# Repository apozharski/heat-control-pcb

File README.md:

# heat-control-pcb
Physical hardware for the Heat/Humidity/general-purpose ecostat.

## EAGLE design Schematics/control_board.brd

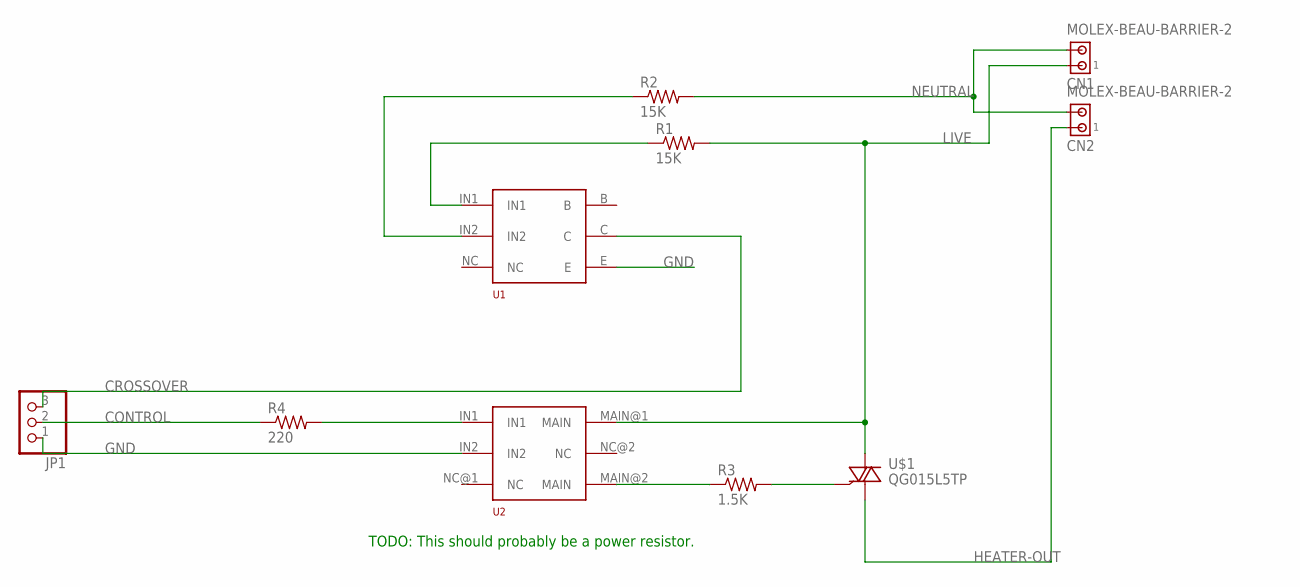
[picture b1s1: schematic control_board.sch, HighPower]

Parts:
CN1, CN2: MOLEX-BEAU-BARRIER-2
JP1: PINHD-1X3/90; 1X03/90
R1, R2: 15K; RSF100
R3: 1.5K; CR-25
R4: 220; CR-25
U1: H11AA4M
U2: MOC3052M
U$1: QG015L5TP

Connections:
CONTROL: JP1.2, R4.P$1 (1)
CROSSOVER: JP1.3, U1.C
GND: JP1.1, U1.E, U2.IN2
HEATER-OUT: CN2.P1 (1), U$1.P$3 (A1)
LIVE: CN1.P1 (1), R1.P$2 (2), U2.MAIN@1 (MAIN), U$1.P$2 (A2)
unnamed: R2.P$1 (1), U1.IN2
unnamed: R1.P$1 (1), U1.IN1
unnamed: R3.P$1 (1), U2.MAIN@2 (MAIN)
unnamed: R3.P$2 (2), U$1.P$1 (G)
unnamed: R4.P$2 (2), U2.IN1
NEUTRAL: CN1.P2 (2), CN2.P2 (2), R2.P$2 (2)

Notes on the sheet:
TODO: This should probably be a power resistor.

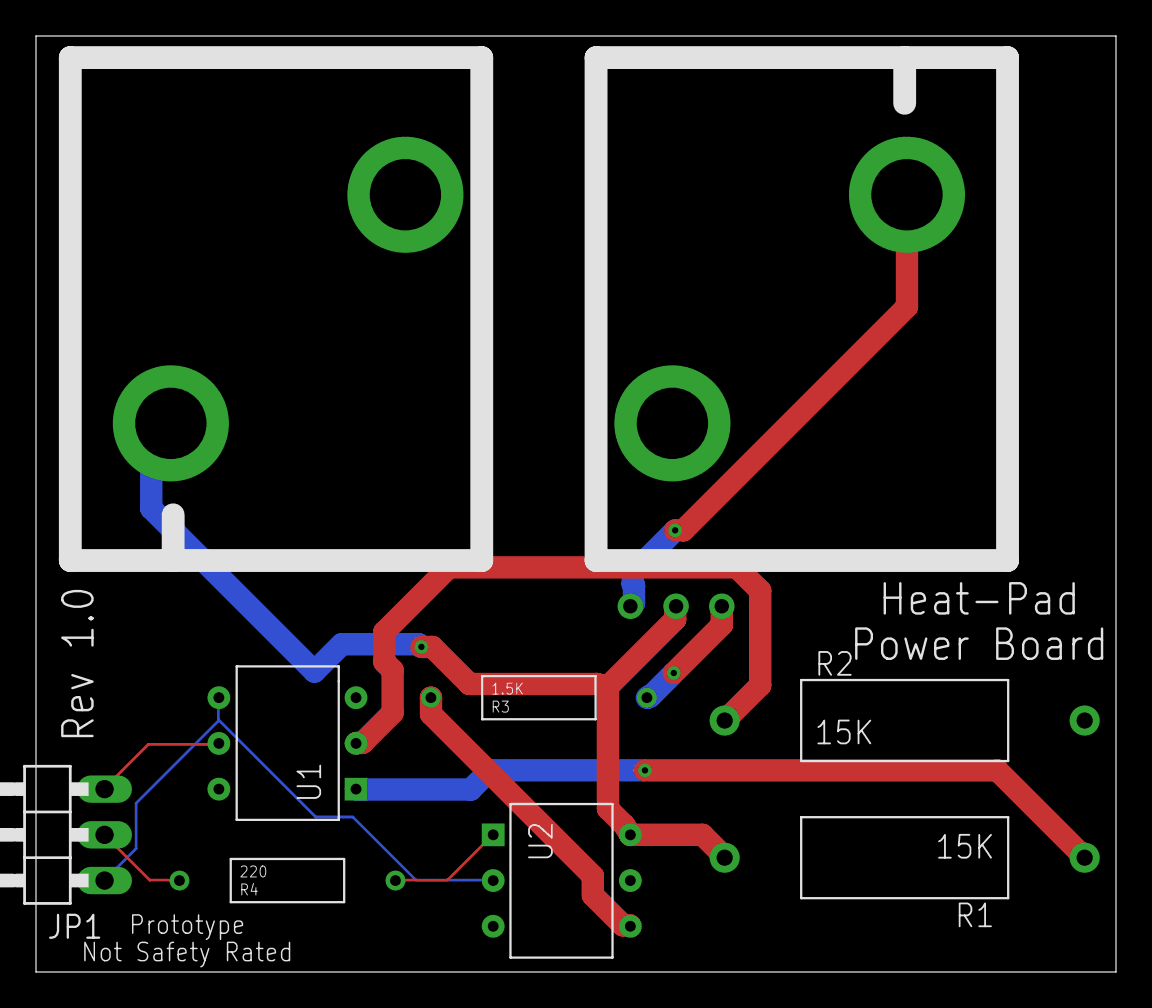
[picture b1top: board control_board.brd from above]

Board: 2 copper layers, 60.0 x 52.0 mm, 10 parts (0 on the bottom side), 11 nets.

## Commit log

2020-06-24 Create initial Readme
2020-06-24 Backlink to CADLAB.io has been added.
2020-06-24 Added Project
2020-06-25 Added some of the dimmer switch circuit
2020-06-25 fix gitignore
2020-06-25 remove backups
2020-07-14 Rev 1.0
2020-07-25 I can definitely read spec sheets.
